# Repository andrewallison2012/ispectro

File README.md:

# Ispectro
Open-source software for an Impedance Spectroscopy (BIS) Device based on Arduino.

To in a venv install:
```
pip install -r requirements.txt 
```

To run:
```
python main.py
```

Qt5 Designer file:
```
ispectro_xml.ui
```

Persistent Settings:
```
config.ini
```

Generate pyQt5 Ui_MainWindow and QtBaseClass classes for python
```
pyuic5 -x ispectro_xml.ui -o ispectro_xml.py
```

Arduino Code for BIS Device
```
firmware.ino
```

KiCad Schematics for Device:
```
impedance_777/impedance_777_r1.pro
```

> Software and firmware for an Impedance Spectroscopy (BIS) Device based on ATMEGA2560 (Arduino) and AD5933
>
> Copyright (C) 2021  Andrew Allison
>
> This program is free software: you can redistribute it and/or modify it under the terms of the GNU Affero General Public License as published by the Free Software Foundation, either version 3 of the License, or (at your option) any later version.
>
> This program is distributed in the hope that it will be useful, but WITHOUT ANY WARRANTY; without even the implied warranty of MERCHANTABILITY or FITNESS FOR A PARTICULAR PURPOSE.  See the GNU Affero General Public License for more details.
>
> You should have received a copy of the GNU Affero General Public License along with this program.  If not, see <http://www.gnu.org/licenses/>.

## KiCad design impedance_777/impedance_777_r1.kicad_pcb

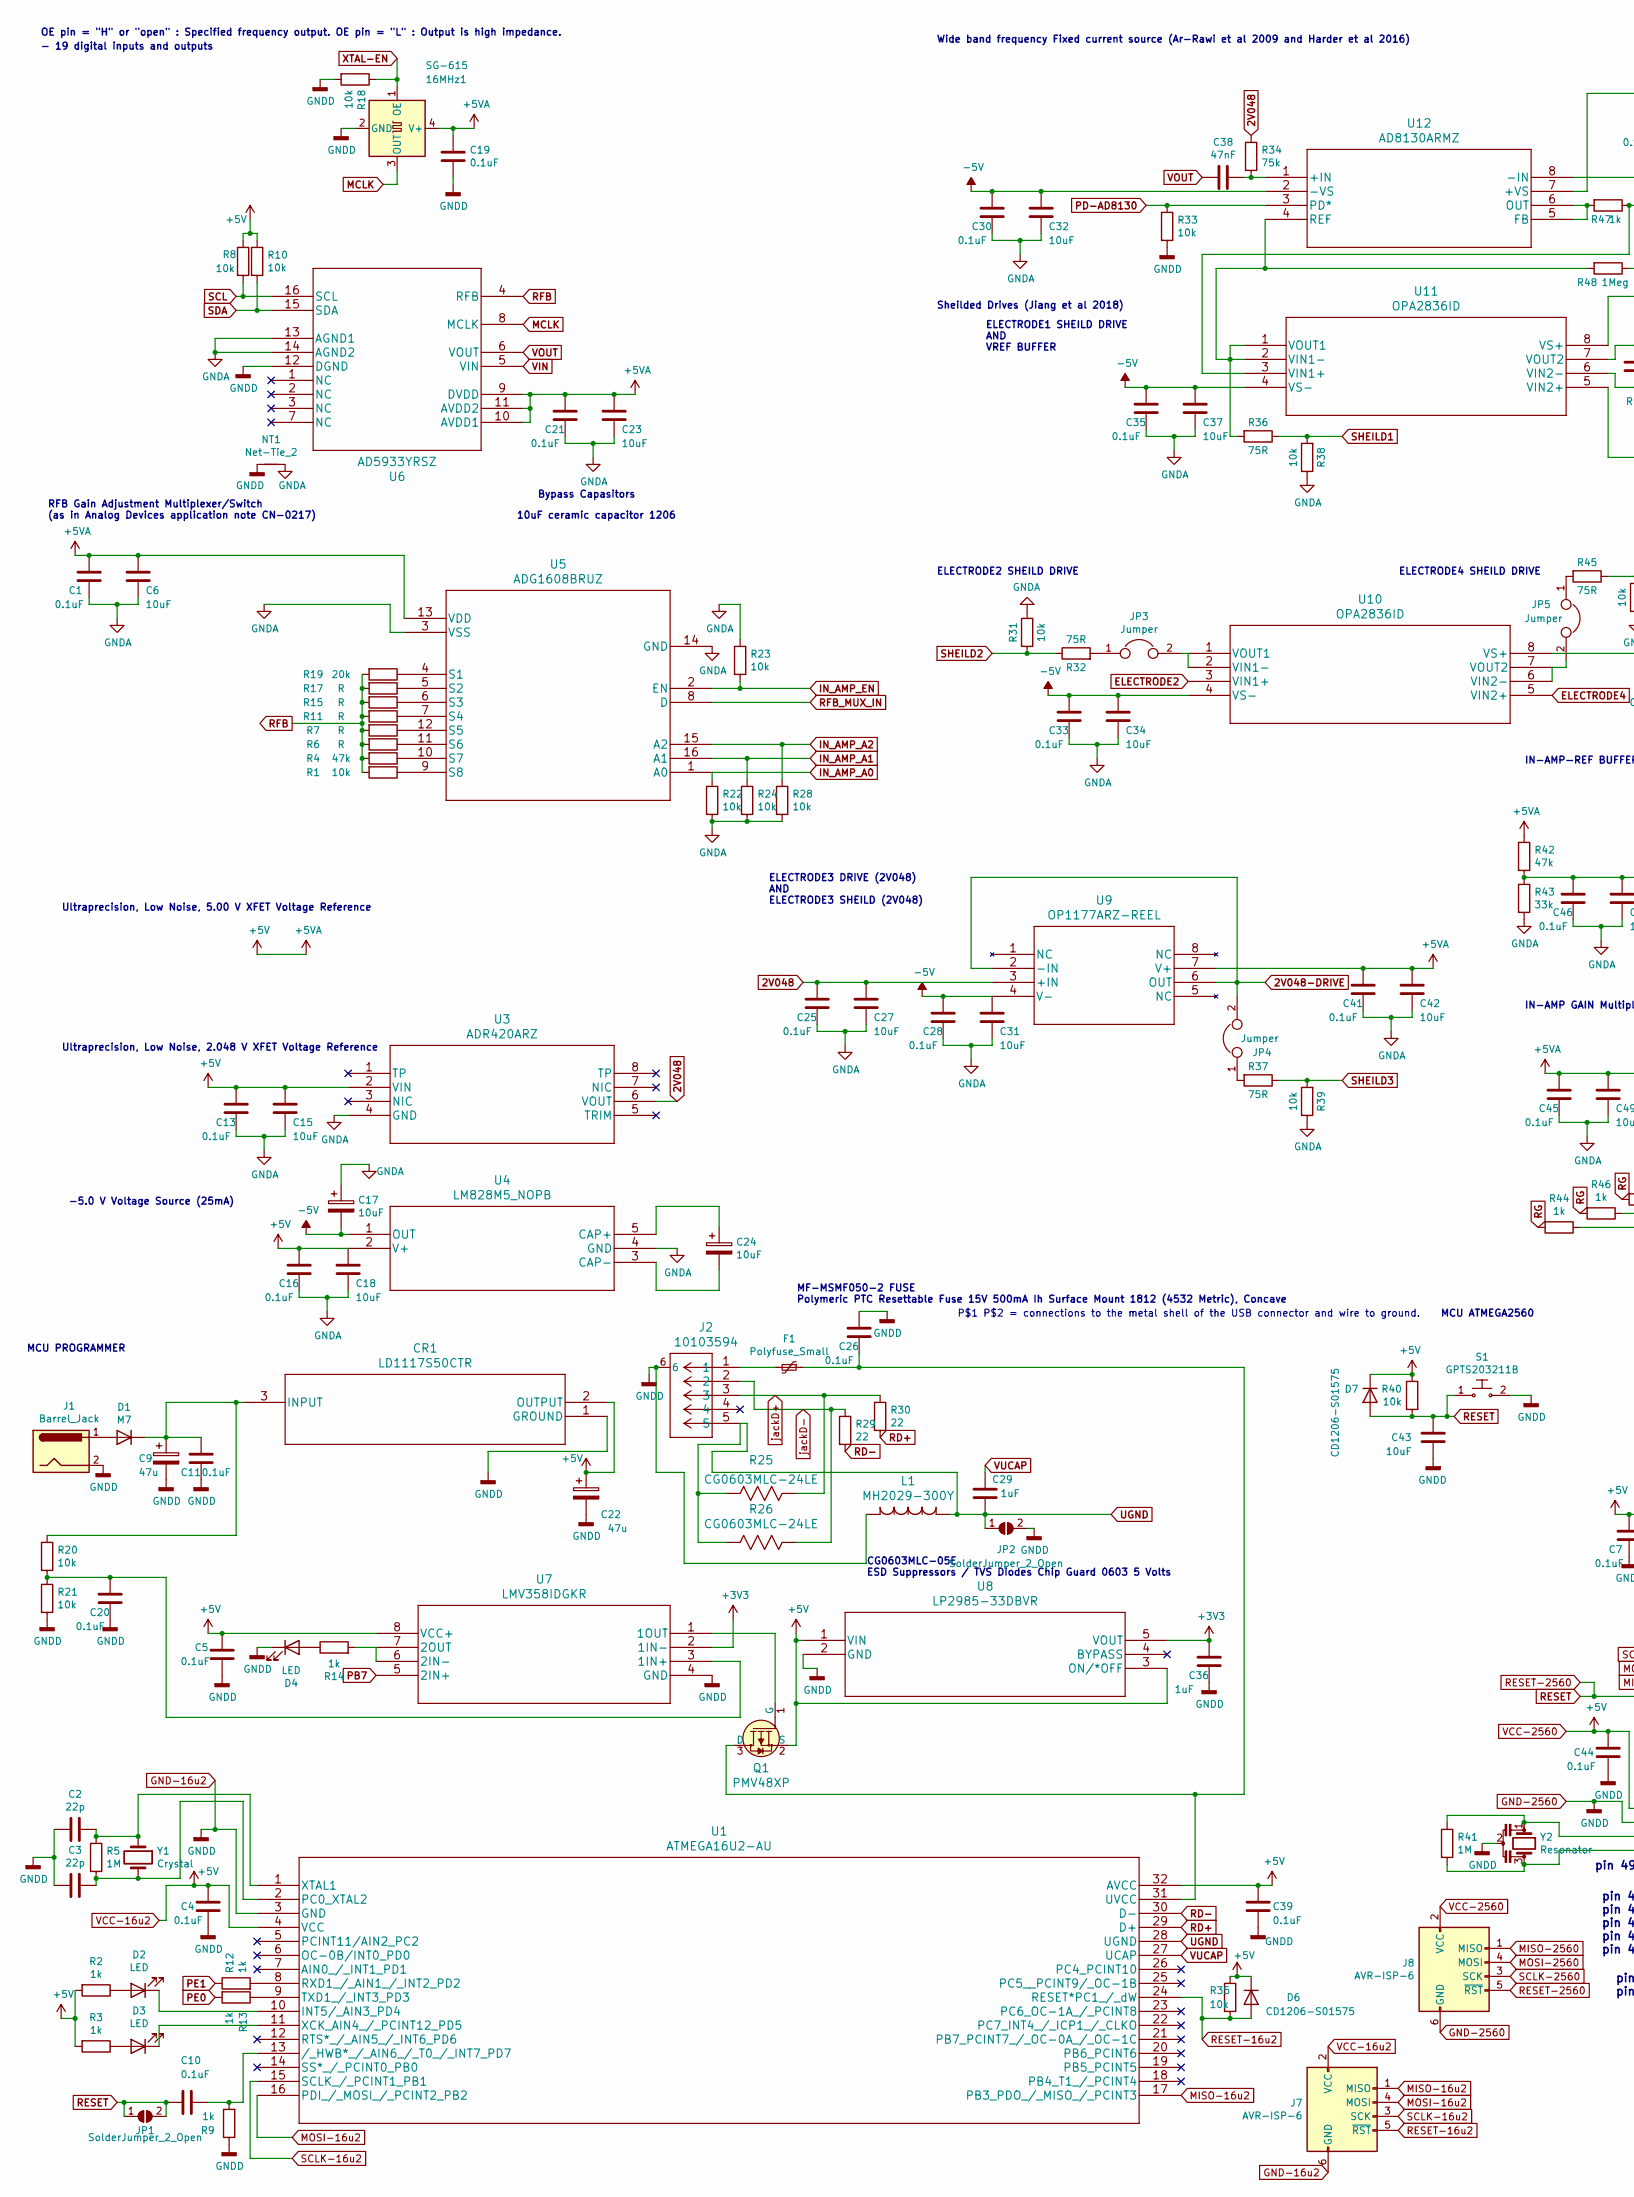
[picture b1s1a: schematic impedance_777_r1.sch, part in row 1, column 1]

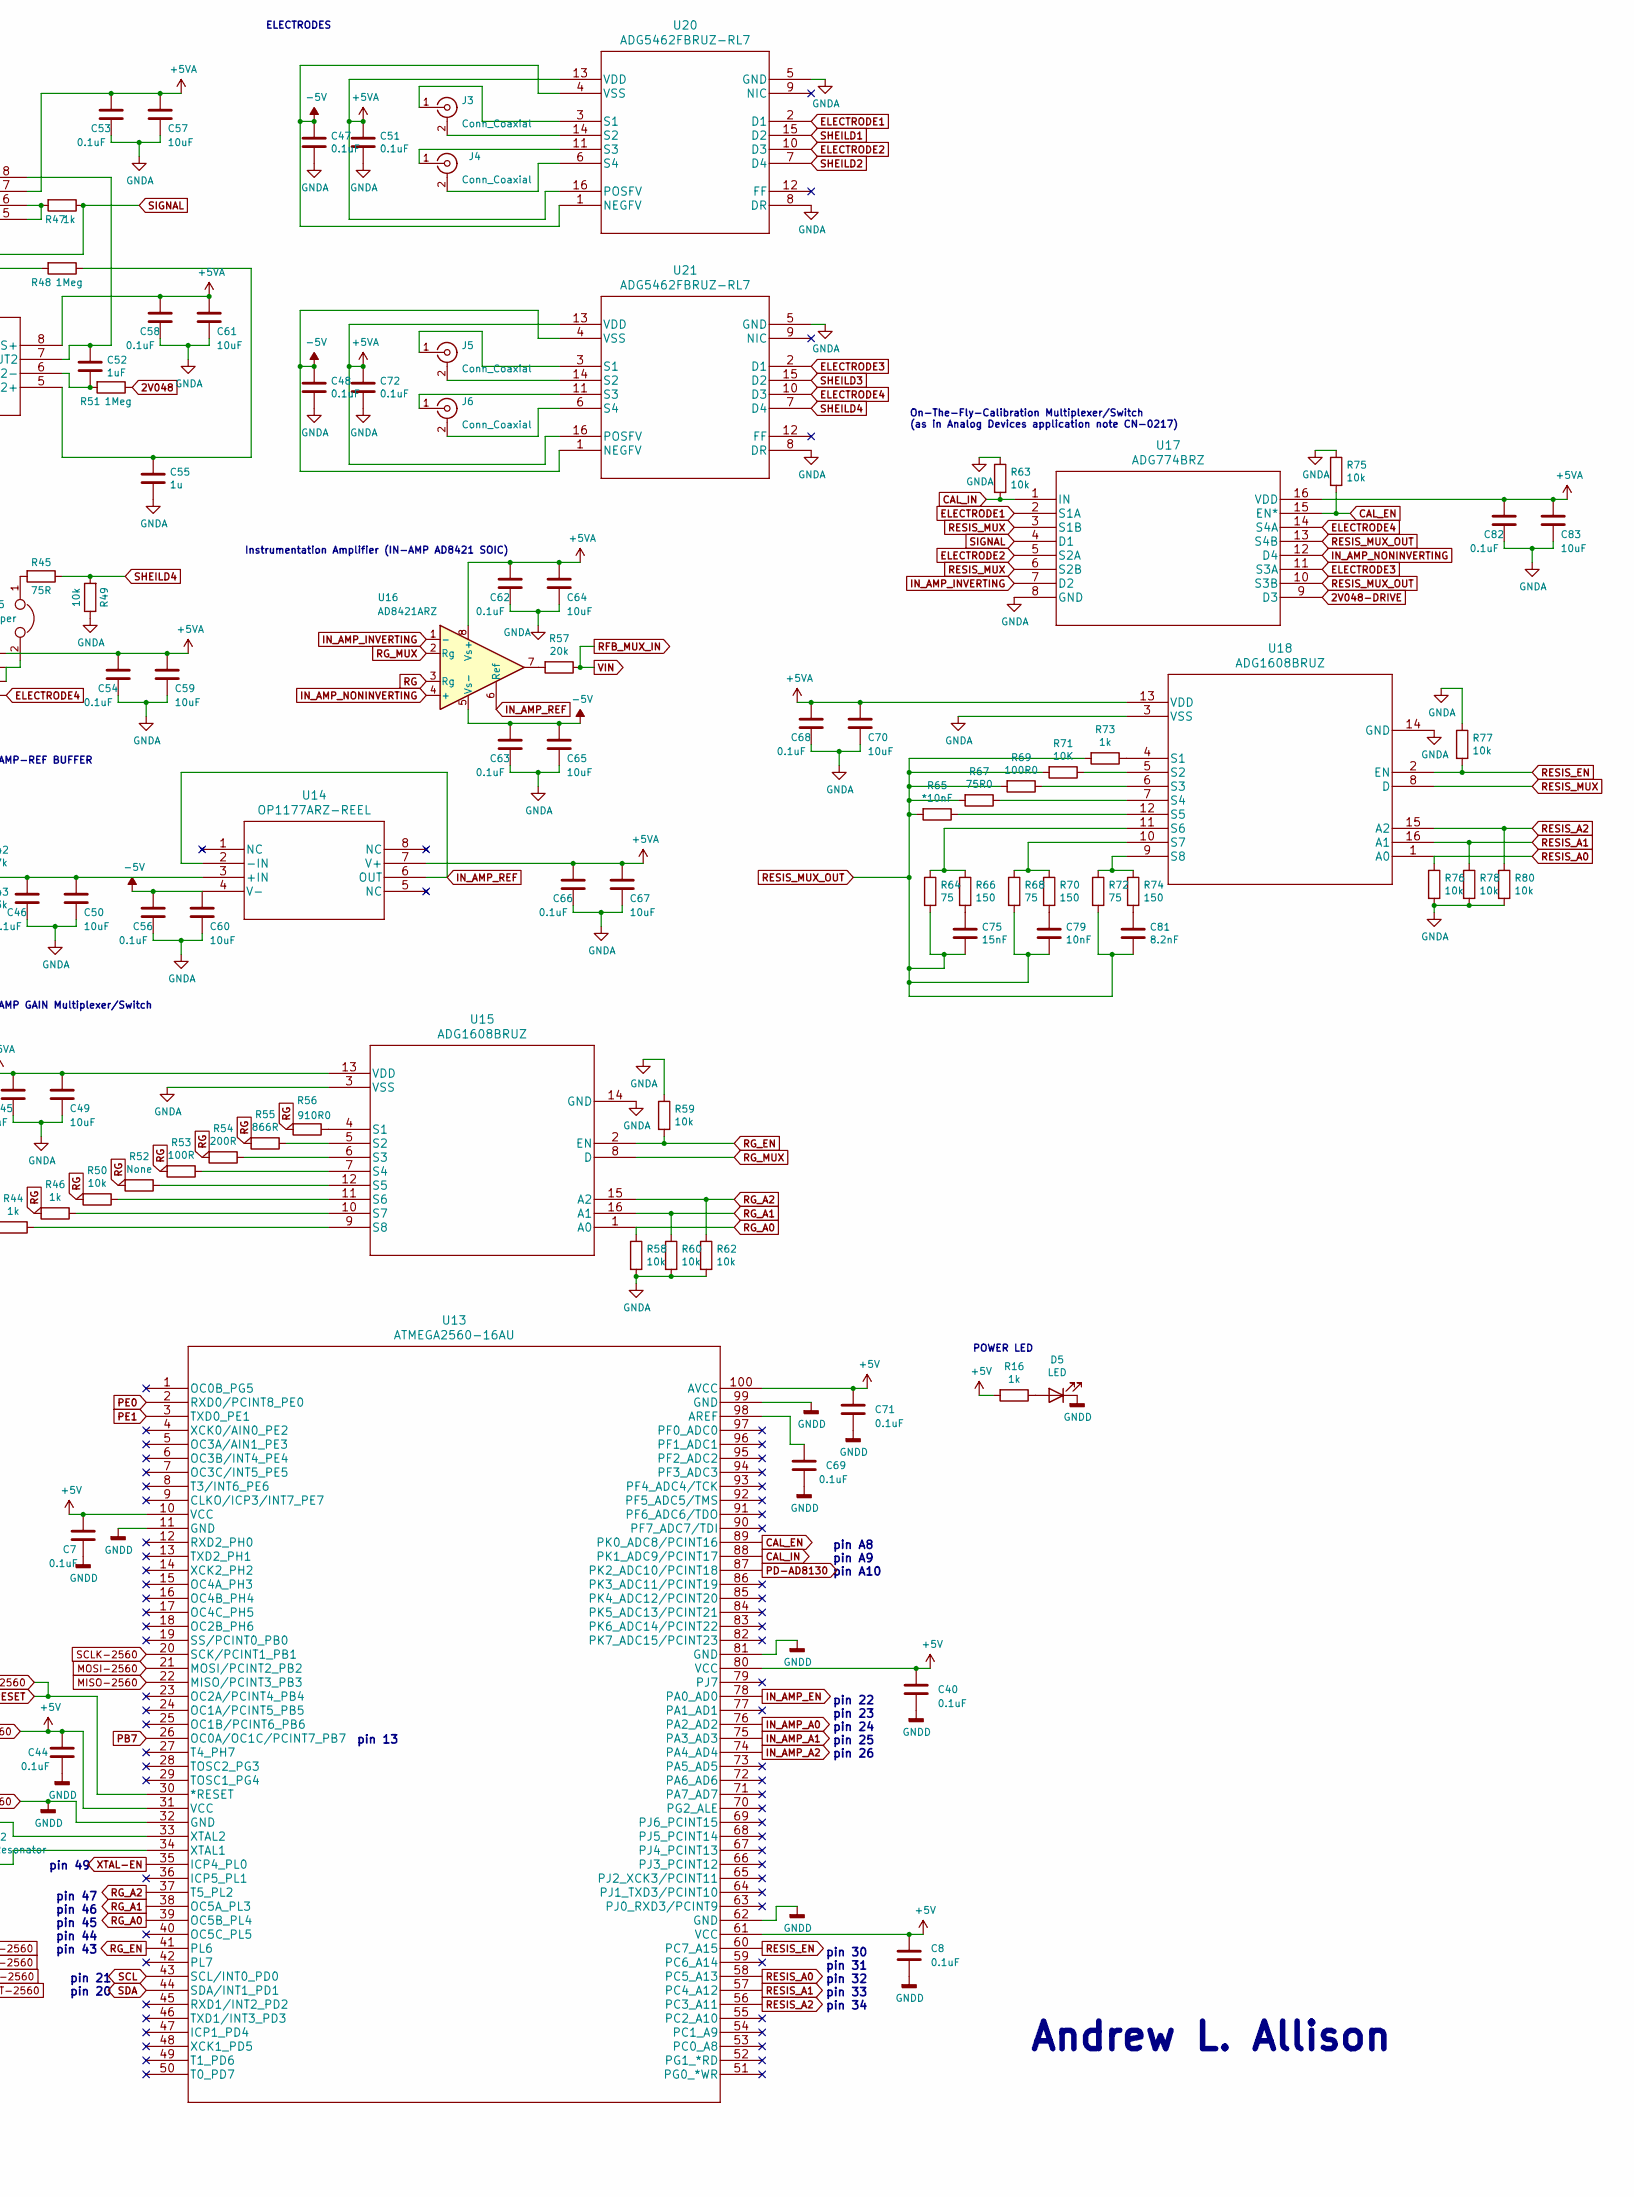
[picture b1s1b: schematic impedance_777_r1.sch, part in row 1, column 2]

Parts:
16MHz1: SG-615; Oscillator_SMD_SeikoEpson_SG8002JA-4Pin_14.0x8.7mm
C1, C4, C5, C7, C8, C10, C11, C13, C16, C19, C20, C21, C25, C26, C28, C30, C33, C35, C39, C40, C41, C44, C45, C46, C47, C48, C51, C53, C54, C56, C58, C62, C63, C66, C68, C69, C71, C72, C82: 0.1uF; C_0805_2012Metric_Pad1.15x1.40mm_HandSolder
C2, C3: 22p; C_0805_2012Metric_Pad1.15x1.40mm_HandSolder
C6, C15, C18, C23, C27, C31, C32, C34, C37, C42, C43, C49, C50, C57, C59, C60, C61, C64, C65, C67, C70, C83: 10uF; C_0805_2012Metric_Pad1.15x1.40mm_HandSolder
C9, C22: 47u; C_0805_2012Metric_Pad1.15x1.40mm_HandSolder
C17, C24: 10uF; CP_Elec_5x5.4
C29, C36, C52: 1uF; C_0805_2012Metric_Pad1.15x1.40mm_HandSolder
C38: 47nF; C_0805_2012Metric_Pad1.15x1.40mm_HandSolder
C55: 1u; C_0805_2012Metric_Pad1.15x1.40mm_HandSolder
C75: 15nF; C_0805_2012Metric_Pad1.15x1.40mm_HandSolder
C79: 10nF; C_0805_2012Metric_Pad1.15x1.40mm_HandSolder
C81: 8.2nF; C_0805_2012Metric_Pad1.15x1.40mm_HandSolder
CR1: LD1117S50CTR; SOT-223-3_TabPin2
D1: M7; D_SMB
D2, D3, D4, D5: LED; LED_0805_2012Metric_Pad1.15x1.40mm_HandSolder
D6, D7: CD1206-S01575; D_1206_3216Metric_Pad1.42x1.75mm_HandSolder
F1: Polyfuse_Small; Fuse_1812_4532Metric_Pad1.30x3.40mm_HandSolder
J1: Barrel_Jack; BarrelJack_CUI_PJ-063AH_Horizontal
J2: 10103594; USB_Micro-B_Amphenol_10103594-0001LF_Horizontal
J3, J4, J5, J6: Conn_Coaxial; 5227161-6.pretty
J7, J8: AVR-ISP-6; IDC-Header_2x03_P2.54mm_Vertical
JP1, JP2: SolderJumper_2_Open; SolderJumper-2_P1.3mm_Open_RoundedPad1.0x1.5mm
JP3, JP4, JP5: Jumper; SolderJumper-2_P1.3mm_Open_RoundedPad1.0x1.5mm
L1: MH2029-300Y; L_0805_2012Metric_Pad1.15x1.40mm_HandSolder
NT1: Net-Tie_2; NetTie-2_SMD_Pad2.0mm
Q1: PMV48XP; SOT-23; MPN AO3401A; Digi-Key_PN 785-1001-1-ND
R1, R8, R10, R18, R20, R21, R22, R23, R24, R28, R31, R33, R35, R38, R39, R40, R49, R50, R58, R59, R60, R62, R63, R75, R76, R77, R78, R80: 10k; R_0805_2012Metric_Pad1.15x1.40mm_HandSolder
R2, R3, R9, R12, R13, R14, R16, R44, R46, R47, R73: 1k; R_0805_2012Metric_Pad1.15x1.40mm_HandSolder
R4, R42: 47k; R_0805_2012Metric_Pad1.15x1.40mm_HandSolder
R5, R41: 1M; R_0805_2012Metric_Pad1.15x1.40mm_HandSolder
R6, R7, R11, R15, R17: R; R_0805_2012Metric_Pad1.15x1.40mm_HandSolder
R19, R57: 20k; R_0805_2012Metric_Pad1.15x1.40mm_HandSolder
R25, R26: CG0603MLC-24LE; R_0603_1608Metric_Pad1.05x0.95mm_HandSolder
R29, R30: 22; R_0805_2012Metric_Pad1.15x1.40mm_HandSolder
R32, R36, R37, R45: 75R; R_0805_2012Metric_Pad1.15x1.40mm_HandSolder
R34: 75k; R_0805_2012Metric_Pad1.15x1.40mm_HandSolder
R43: 33k; R_0805_2012Metric_Pad1.15x1.40mm_HandSolder
R48, R51: 1Meg; R_0805_2012Metric_Pad1.15x1.40mm_HandSolder
R52: None; R_0805_2012Metric_Pad1.15x1.40mm_HandSolder
R53: 100R; R_0805_2012Metric_Pad1.15x1.40mm_HandSolder
R54: 200R; R_0805_2012Metric_Pad1.15x1.40mm_HandSolder
R55: 866R; R_0805_2012Metric_Pad1.15x1.40mm_HandSolder
R56: 910R0; R_0805_2012Metric_Pad1.15x1.40mm_HandSolder
R64, R68, R72: 75; R_0805_2012Metric_Pad1.15x1.40mm_HandSolder
R65: *10nF; R_0805_2012Metric_Pad1.15x1.40mm_HandSolder
R66, R70, R74: 150; R_0805_2012Metric_Pad1.15x1.40mm_HandSolder
R67: 75R0; R_0805_2012Metric_Pad1.15x1.40mm_HandSolder
R69: 100R0; R_0805_2012Metric_Pad1.15x1.40mm_HandSolder
R71: 10K; R_0805_2012Metric_Pad1.15x1.40mm_HandSolder
S1: GPTS203211B; SW_Tactile_SPST_Angled_PTS645Vx58-2LFS; MPN GPTS203211B; Digi-Key_PN CW181-ND
U1: ATMEGA16U2-AU
U3: ADR420ARZ
U4: LM828M5_NOPB; LM828M5&slash_NOPB
U5, U15, U18: ADG1608BRUZ
U6: AD5933YRSZ
U7: LMV358IDGKR
U8: LP2985-33DBVR
U9, U14: OP1177ARZ-REEL
U10, U11: OPA2836ID
U12: AD8130ARMZ
U13: ATMEGA2560-16AU
U16: AD8421ARZ
U17: ADG774BRZ
U20, U21: ADG5462FBRUZ-RL7
Y1: Crystal; Crystal_HC18-U_Vertical
Y2: Resonator; Resonator_SMD_muRata_CSTxExxV-3Pin_3.0x1.1mm_HandSoldering

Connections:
2V048: C25.1, C27.1, R34.1, R51.1, U3.6 (VOUT), U9.3 (+IN)
2V048-DRIVE: JP4.2, U9.2 (-IN), U9.6 (OUT), U17.9 (D3)
+3V3: C36.1, U7.2 (1IN-), U8.5 (VOUT)
-5V: C17.2, C28.1, C30.1, C31.1, C32.1, C33.1, C34.1, C35.1, C37.1, C47.1, C48.1, C56.1, C60.1, C63.1, C65.1, U4.1 (OUT), U9.4 (V-), U10.4 (VS-), U11.4 (VS-), U12.2 (-VS), U14.4 (V-), U16.5 (Vs-), U20.1 (NEGFV), U20.4 (VSS), U21.1 (NEGFV), U21.4 (VSS)
CAL_EN: R75.2, U13.89 (PK0_ADC8/PCINT16), U17.15 (EN*)
CAL_IN: R63.2, U13.88 (PK1_ADC9/PCINT17), U17.1 (IN)
ELECTRODE1: U17.2 (S1A), U20.2 (D1)
ELECTRODE2: U10.3 (VIN1+), U17.5 (S2A), U20.10 (D3)
ELECTRODE3: U17.11 (S3A), U21.2 (D1)
ELECTRODE4: U10.5 (VIN2+), U17.14 (S4A), U21.10 (D3)
GND-16u2: 16MHz1.2 (GND), C2.2, C3.2, C4.2, C5.2, C7.2, C8.2, C9.2, C11.2, C19.2, C20.2, C22.2, C26.1, C36.2, C39.2, C40.2, C43.2, C44.2, C69.2, C71.2, CR1.1 (GROUND), D4.1 (K), D5.1 (K), J1.2, J2.6, J7.6 (GND), J8.6 (GND), JP2.2 (B), L1.2, NT1.1, R9.1, R18.2, R21.2, R33.2, S1.2, U1.3 (GND), U6.12 (DGND), U7.4 (GND), U8.2 (GND), U13.11 (GND), U13.32 (GND), U13.62 (GND), U13.81 (GND), U13.99 (GND), Y2.2
GNDA: C1.2, C6.2, C13.2, C15.2, C16.2, C17.1, C18.2, C21.2, C23.2, C25.2, C27.2, C28.2, C30.2, C31.2, C32.2, C33.2, C34.2, C35.2, C37.2, C41.2, C42.2, C45.2, C46.2, C47.2, C48.2, C49.2, C50.2, C51.2, C53.2, C54.2, C55.1, C56.2, C57.2, C58.2, C59.2, C60.2, C61.2, C62.2, C63.2, C64.2, C65.2, C66.2, C67.2, C68.2, C70.2, C72.2, C82.2, C83.2, NT1.2, R22.2, R23.1, R24.2, R28.2, R31.1, R38.1, R39.1, R43.2, R49.1, R58.2, R59.1, R60.2, R62.2, R63.1, R75.1, R76.2, R77.1, R78.2, R80.2, U3.4 (GND), U4.4 (GND), U5.3 (VSS), U5.14 (GND), U6.13 (AGND1), U6.14 (AGND2), U15.3 (VSS), U15.14 (GND), U17.8 (GND), U18.3 (VSS), U18.14 (GND), U20.5 (GND), U20.8 (DR), U21.5 (GND), U21.8 (DR)
IN_AMP_A0: R22.1, U5.1 (A0), U13.76 (PA2_AD2)
IN_AMP_A1: R24.1, U5.16 (A1), U13.75 (PA3_AD3)
IN_AMP_A2: R28.1, U5.15 (A2), U13.74 (PA4_AD4)
IN_AMP_EN: R23.2, U5.2 (EN), U13.78 (PA0_AD0)
IN_AMP_INVERTING: U16.1 (-), U17.7 (D2)
IN_AMP_NONINVERTING: U16.4 (+), U17.12 (D4)
IN_AMP_REF: U14.2 (-IN), U14.6 (OUT), U16.6 (Ref)
MCLK: 16MHz1.3 (OUT), U6.8 (MCLK)
MISO-16u2: J7.1 (MISO), U1.17 (PB3_PDO_/_MISO_/_PCINT3)
MISO-2560: J8.1 (MISO), U13.22 (MISO/PCINT3_PB3)
MOSI-16u2: J7.4 (MOSI), U1.16 (PDI_/_MOSI_/_PCINT2_PB2)
MOSI-2560: J8.4 (MOSI), U13.21 (MOSI/PCINT2_PB2)
unnamed: C2.1, R5.1, U1.1 (XTAL1), Y1.1
unnamed: C3.1, R5.2, U1.2 (PC0_XTAL2), Y1.2
unnamed: C10.1, R9.2, U1.13 (/_HWB*_/_AIN6_/_T0_/_INT7_PD7)
unnamed: C9.1, C11.1, CR1.3 (INPUT), D1.2 (K), R20.1
unnamed: C20.1, R20.2, R21.1, U7.3 (1IN+)
unnamed: C24.1, U4.5 (CAP+)
unnamed: C24.2, U4.3 (CAP-)
unnamed: C26.2, F1.1, Q1.3 (D), U1.31 (UVCC)
unnamed: C38.1, R34.2, U12.1 (+IN)
unnamed: C46.1, C50.1, R42.2, R43.1, U14.3 (+IN)
unnamed: C52.1, R51.2, U11.6 (VIN2-)
unnamed: C52.2, U11.7 (VOUT2), U12.8 (-IN)
unnamed: C55.2, R48.1, U11.5 (VIN2+)
unnamed: C69.1, U13.98 (AREF)
unnamed: C75.1, R66.2
unnamed: C79.1, R70.2
unnamed: C81.1, R74.2
unnamed: D1.1 (A), J1.1
unnamed: D2.1 (K), U1.10 (INT5/_AIN3_PD4)
unnamed: D2.2 (A), R2.1
unnamed: D3.1 (K), U1.11 (XCK_AIN4_/_PCINT12_PD5)
unnamed: D3.2 (A), R3.1
unnamed: D4.2 (A), R14.1
unnamed: D5.2 (A), R16.1
unnamed: F1.2, J2.1
unnamed: J3.1 (In), U20.3 (S1)
unnamed: J3.2 (Ext), U20.14 (S2)
unnamed: J4.1 (In), U20.11 (S3)
unnamed: J4.2 (Ext), U20.6 (S4)
unnamed: J5.1 (In), U21.3 (S1)
unnamed: J5.2 (Ext), U21.14 (S2)
unnamed: J6.1 (In), U21.11 (S3)
unnamed: J6.2 (Ext), U21.6 (S4)
unnamed: JP3.1, R32.2
unnamed: JP3.2, U10.1 (VOUT1), U10.2 (VIN1-)
unnamed: JP4.1, R37.2
unnamed: JP5.1, R45.2
unnamed: JP5.2, U10.6 (VIN2-), U10.7 (VOUT2)
unnamed: Q1.1 (G), U7.1 (1OUT)
unnamed: R1.1, U5.9 (S8)
unnamed: R4.1, U5.10 (S7)
unnamed: R6.1, U5.11 (S6)
unnamed: R7.1, U5.12 (S5)
unnamed: R11.1, U5.7 (S4)
unnamed: R12.2, U1.8 (RXD1_/_AIN1_/_INT2_PD2)
unnamed: R13.1, U1.9 (TXD1_/_INT3_PD3)
unnamed: R14.2, U7.6 (2IN-), U7.7 (2OUT)
unnamed: R15.1, U5.6 (S3)
unnamed: R17.1, U5.5 (S2)
unnamed: R19.1, U5.4 (S1)
unnamed: R36.2, R48.2, U11.1 (VOUT1), U11.2 (VIN1-), U12.4 (REF)
unnamed: R41.1, U13.33 (XTAL2), Y2.1
unnamed: R41.2, U13.34 (XTAL1), Y2.3
unnamed: R44.1, U15.9 (S8)
unnamed: R46.1, U15.10 (S7)
unnamed: R47.2, U12.5 (FB), U12.6 (OUT)
unnamed: R50.1, U15.11 (S6)
unnamed: R52.1, U15.12 (S5)
unnamed: R53.1, U15.7 (S4)
unnamed: R54.1, U15.6 (S3)
unnamed: R55.1, U15.5 (S2)
unnamed: R56.1, U15.4 (S1)
unnamed: R57.2, U16.7
unnamed: R64.1, R66.1, U18.11 (S6)
unnamed: R65.1, U18.12 (S5)
unnamed: R67.1, U18.7 (S4)
unnamed: R68.1, R70.1, U18.10 (S7)
unnamed: R69.1, U18.6 (S3)
unnamed: R71.1, U18.5 (S2)
unnamed: R72.1, R74.1, U18.9 (S8)
unnamed: R73.1, U18.4 (S1)
PB7: U7.5 (2IN+), U13.26 (OC0A/OC1C/PCINT7_PB7)
PD-AD8130: R33.1, U12.3 (PD*), U13.87 (PK2_ADC10/PCINT18)
PE0: R13.2, U13.2 (RXD0/PCINT8_PE0)
PE1: R12.1, U13.3 (TXD0_PE1)
RD+: R30.2, U1.29 (D+)
RD-: R29.2, U1.30 (D-)
RESET: C10.2, C43.1, D7.1 (A), J8.5 (~RST), JP1.1 (A), JP1.2 (B), R40.2, S1.1, U13.30 (*RESET)
RESET-16u2: D6.1 (A), J7.5 (~RST), R35.2, U1.24 (RESET*PC1_/_dW)
RESIS_A0: R76.1, U13.58 (PC5_A13), U18.1 (A0)
RESIS_A1: R78.1, U13.57 (PC4_A12), U18.16 (A1)
RESIS_A2: R80.1, U13.56 (PC3_A11), U18.15 (A2)
RESIS_EN: R77.2, U13.60 (PC7_A15), U18.2 (EN)
RESIS_MUX: U17.3 (S1B), U17.6 (S2B), U18.8 (D)
RESIS_MUX_OUT: C75.2, C79.2, C81.2, R64.2, R65.2, R67.2, R68.2, R69.2, R71.2, R72.2, R73.2, U17.10 (S3B), U17.13 (S4B)
RFB: R1.2, R4.2, R6.2, R7.2, R11.2, R15.2, R17.2, R19.2, U6.4 (RFB)
RFB_MUX_IN: R57.1, U5.8 (D), U6.5 (VIN)
RG: R44.2, R46.2, R50.2, R52.2, R53.2, R54.2, R55.2, R56.2, U16.3 (Rg)
RG_A0: R58.1, U13.39 (OC5B_PL4), U15.1 (A0)
RG_A1: R60.1, U13.38 (OC5A_PL3), U15.16 (A1)
RG_A2: R62.1, U13.37 (T5_PL2), U15.15 (A2)
RG_EN: R59.2, U13.41 (PL6), U15.2 (EN)
RG_MUX: U15.8 (D), U16.2 (Rg)
SCL: R8.2, U6.16 (SCL), U13.43 (SCL/INT0_PD0)
SCLK-16u2: J7.3 (SCK), U1.15 (SCLK_/_PCINT1_PB1)
SCLK-2560: J8.3 (SCK), U13.20 (SCK/PCINT1_PB1)
SDA: R10.2, U6.15 (SDA), U13.44 (SDA/INT1_PD1)
SHEILD1: R36.1, R38.2, U20.15 (D2)
SHEILD2: R31.2, R32.1, U20.7 (D4)
SHEILD3: R37.1, R39.2, U21.15 (D2)
SHEILD4: R45.1, R49.2, U21.7 (D4)
SIGNAL: R47.1, U11.3 (VIN1+), U17.4 (D1)
UGND: C29.1, J2.5, JP2.1 (A), L1.1, R25.2, R26.2, U1.28 (UGND)
VCC-16u2: 16MHz1.4 (V+), C1.1, C4.1, C5.1, C6.1, C7.1, C8.1, C13.1, C15.1, C16.1, C18.1, C19.1, C21.1, C22.1, C23.1, C39.1, C40.1, C41.1, C42.1, C44.1, C45.1, C49.1, C51.1, C53.1, C54.1, C57.1, C58.1, C59.1, C61.1, C62.1, C64.1, C66.1, C67.1, C68.1, C70.1, C71.1, C72.1, C82.1, C83.1, CR1.2 (OUTPUT), D6.2 (K), D7.2 (K), J7.2 (VCC), J8.2 (VCC), Q1.2 (S), R2.2, R3.2, R8.1, R10.1, R16.2, R35.1, R40.1, R42.1, U1.4 (VCC), U1.32 (AVCC), U3.2 (VIN), U4.2 (V+), U5.13 (VDD), U6.9 (DVDD), U6.10 (AVDD1), U6.11 (AVDD2), U7.8 (VCC+), U8.1 (VIN), U8.3 (ON/*OFF), U9.7 (V+), U10.8 (VS+), U11.8 (VS+), U12.7 (+VS), U13.10 (VCC), U13.31 (VCC), U13.61 (VCC), U13.80 (VCC), U13.100 (AVCC), U14.7 (V+), U15.13 (VDD), U16.8 (Vs+), U17.16 (VDD), U18.13 (VDD), U20.13 (VDD), U20.16 (POSFV), U21.13 (VDD), U21.16 (POSFV)
VOUT: C38.2, U6.6 (VOUT)
VUCAP: C29.2, U1.27 (UCAP)
XTAL-EN: 16MHz1.1 (OE), R18.1, U13.35 (ICP4_PL0)
jackD+: J2.3, R25.1, R30.1
jackD-: J2.2, R26.1, R29.1

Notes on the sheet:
OE pin = "H" or "open" : Specified frequency output. OE pin = "L" : Output is high impedance.
Wide band frequency Fixed current source (Ar-Rawi et al 2009 and Harder et al 2016)
Bypass Capasitors
10uF ceramic capacitor 1206
ELECTRODE1 SHEILD DRIVE AND VREF BUFFER
Ultraprecision, Low Noise, 2.048 V XFET Voltage Reference
Ultraprecision, Low Noise, 5.00 V XFET Voltage Reference
-5.0 V Voltage Source (25mA)
Sheilded Drives (Jiang et al 2018)
IN-AMP-REF BUFFER
Instrumentation Amplifier (IN-AMP AD8421 SOIC)
On-The-Fly-Calibration Multiplexer/Switch (as in Analog Devices application note CN-0217)
RFB Gain Adjustment Multiplexer/Switch (as in Analog Devices application note CN-0217)
IN-AMP GAIN Multiplexer/Switch
ELECTRODES
ELECTRODE3 DRIVE (2V048) AND ELECTRODE3 SHEILD (2V048)
ELECTRODE4 SHEILD DRIVE
ELECTRODE2 SHEILD DRIVE
- 19 digital inputs and outputs
pin 22 pin 23 pin 24 pin 25 pin 26
pin 30 pin 31 pin 32 pin 33 pin 34
pin 47 pin 46 pin 45 pin 44 pin 43
pin 21 pin 20
pin A8 pin A9 pin A10
pin 49
CG0603MLC-05E ESD Suppressors / TVS Diodes Chip Guard 0603 5 Volts
MF-MSMF050-2 FUSE Polymeric PTC Resettable Fuse 15V 500mA Ih Surface Mount 1812 (4532 Metric), Concave
POWER LED
MCU PROGRAMMER
MCU ATMEGA2560
P$1 P$2 = connections to the metal shell of the USB connector and wire to ground.
pin 13
Andrew L. Allison

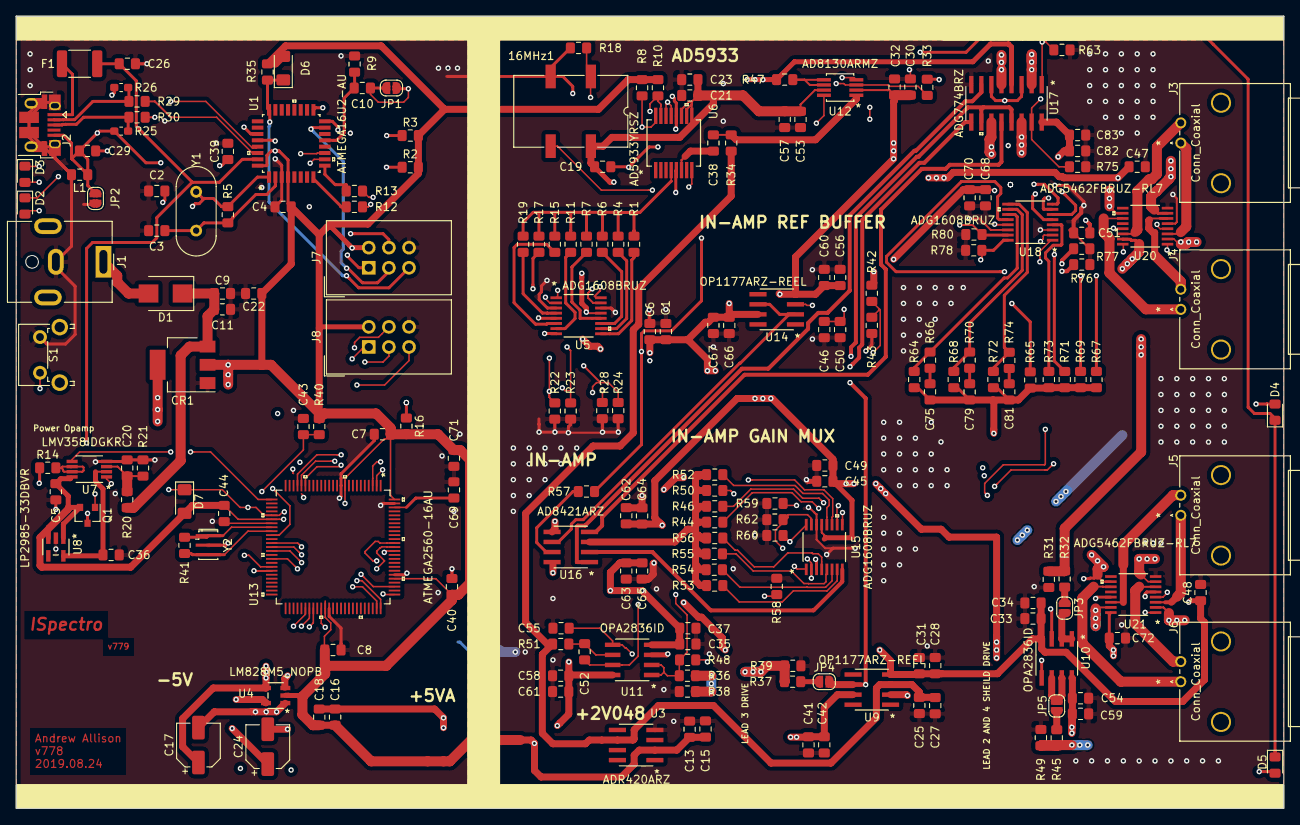
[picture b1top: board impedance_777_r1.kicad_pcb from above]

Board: 4 copper layers, 160.0 x 100.0 mm, 200 parts (1 on the bottom side), 133 nets.

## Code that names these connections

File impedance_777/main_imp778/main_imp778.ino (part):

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#define STATUS_REG 0x8F


// const float MCLK = 16.776*pow(10,6);// AD5933 Internal Clock Speed 16.776 MHz

const float MCLK = 16.000*pow(10,6);// AD5933 External Precision Clock Speed 16.000 MHz
const float start_freq = 1*pow(10,3);// Set start freq, < 100Khz
const float incre_freq = 1*pow(10,3);// Set freq increment
const int incre_num = 99;// Set number of increments,< 511
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  pinMode(A10, OUTPUT); // PD-AD8130 ENABLE CURRENT SOURCE

  // ADG774
  pinMode(A8, OUTPUT); // CAL_EN ADG774 CALIBRATION OR LEAD SELECTION 
  pinMode(A9, OUTPUT); // CAL_IN ADG774 CALIBRATION OR LEAD SELECTION 

  // ADG1608-1
  pinMode(30, OUTPUT); // RESIS_EN ADG1608 R/RC CALIBRATION SELECTION 
  pinMode(32, OUTPUT); // RESIS_A0 ADG1608 R/RC CALIBRATION SELECTION
  pinMode(33, OUTPUT); // RESIS_A1 ADG1608 R/RC CALIBRATION SELECTION
  pinMode(34, OUTPUT); // RESIS_A2 ADG1608 R/RC CALIBRATION SELECTION

  // ADG1608-2
  pinMode(43, OUTPUT); // RG_EN ADG1608 IN-AMP RESISTOR GAIN SELECTION
  pinMode(45, OUTPUT); // RG_A0 ADG1608 IN-AMP RESISTOR GAIN SELECTION
  pinMode(46, OUTPUT); // RG_A1 ADG1608 IN-AMP RESISTOR GAIN SELECTION
  pinMode(47, OUTPUT); // RG_A2 ADG1608 IN-AMP RESISTOR GAIN SELECTION

  // ADG1608-3
  pinMode(22, OUTPUT); // IN_AMP_EN ADG1608 RFB SELECTION
  pinMode(24, OUTPUT); // IN_AMP_A0 ADG1608 RFB SELECTION
  pinMode(25, OUTPUT); // IN_AMP_A1 ADG1608 RFB SELECTION
  pinMode(26, OUTPUT); // IN_AMP_A2 ADG1608 RFB SELECTION

  writeData(CTRL_REG,0x0);   //nop - clear ctrl-reg
  writeData(CTRL_REG2,0x10);   //reset ctrl register
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
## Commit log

2021-05-18 null
2021-05-19 Multithreading and Non-blocking GUI
2021-07-07 Add files via upload
    Gerbers for https://jlcpcb.com/ produced 2021_07_06

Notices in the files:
README.md:
License: GPL v3
parts and their libraries:
Copyright 2016 Accelerated Designs. All rights reserved.
